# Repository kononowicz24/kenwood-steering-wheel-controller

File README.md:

# kenwood-steering-wheel-controller
This is a project to adapt the Audi A8 D2 FL multifunction steering wheel to be able to control a Kenwood car audio from the steering wheel controls. 
The large part of the code bases on https://init6.pomorze.pl/projects/kenwood_ford/ and was adapted to feature pin change interrupts on key presses.

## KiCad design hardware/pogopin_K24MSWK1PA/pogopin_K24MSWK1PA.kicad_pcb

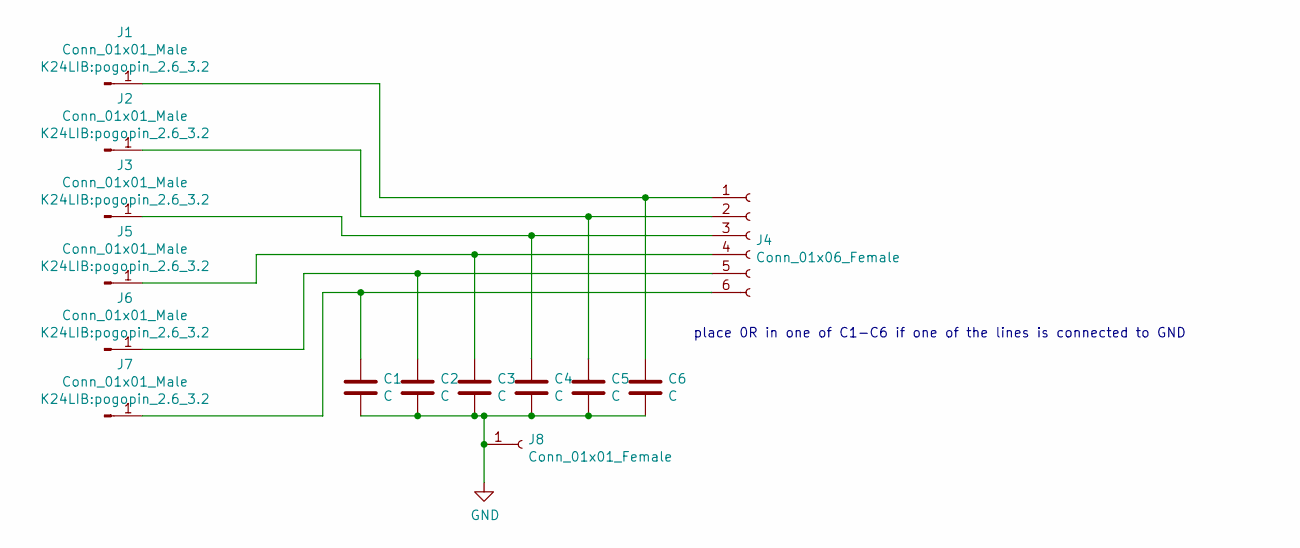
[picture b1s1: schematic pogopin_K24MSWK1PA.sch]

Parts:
C1, C2, C3, C4, C5, C6: C; C_0805_2012Metric
J1, J2, J3, J5, J6, J7: Conn_01x01_Male; pogopin_2.6_3.2
J4: Conn_01x06_Female; JST_PH_S6B-PH-K_1x06_P2.00mm_Horizontal
J8: Conn_01x01_Female; SolderWire-0.75sqmm_1x01_D1.25mm_OD3.5mm

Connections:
GND: C1.2, C2.2, C3.2, C4.2, C5.2, C6.2, J8.1
unnamed: C1.1, J4.6, J7.1
unnamed: C2.1, J4.5, J6.1
unnamed: C3.1, J4.4, J5.1
unnamed: C4.1, J3.1, J4.3
unnamed: C5.1, J2.1, J4.2
unnamed: C6.1, J1.1, J4.1

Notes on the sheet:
place 0R in one of C1-C6 if one of the lines is connected to GND

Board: 2 copper layers, 14 parts (0 on the bottom side), 7 nets, no tracks yet.

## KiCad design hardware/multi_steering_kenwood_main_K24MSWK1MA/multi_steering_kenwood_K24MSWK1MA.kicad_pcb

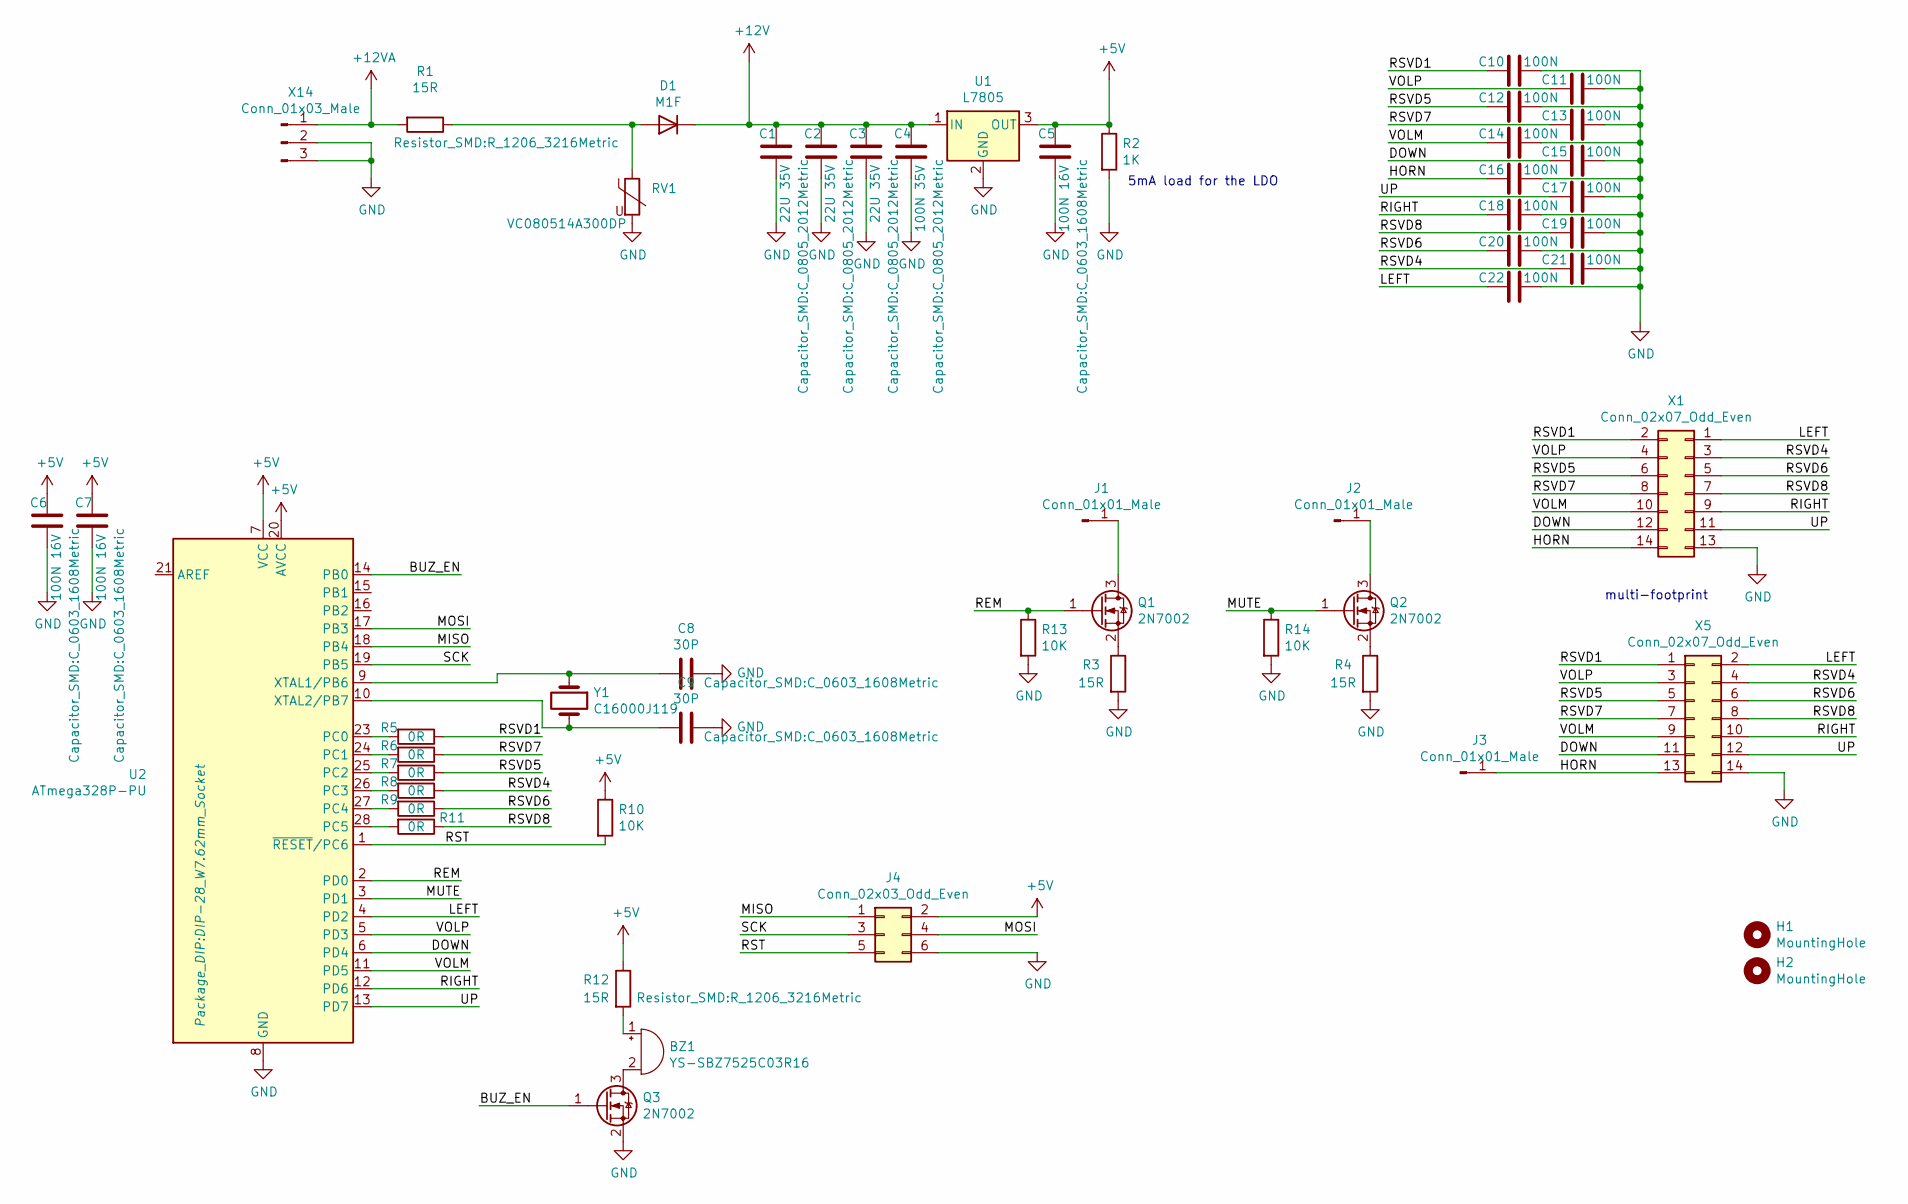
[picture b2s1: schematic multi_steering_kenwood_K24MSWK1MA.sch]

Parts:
BZ1: YS-SBZ7525C03R16; PUIAudio_SMT_0825_S_4_R
C1, C2, C3: 22U 35V; C_0805_2012Metric
C4: 100N 35V; C_0805_2012Metric
C5, C6, C7: 100N 16V; C_0603_1608Metric
C8, C9: 30P; C_0603_1608Metric
C10, C11, C12, C13, C14, C15, C16, C17, C18, C19, C20, C21, C22: 100N; C_0603_1608Metric
D1: M1F; D_SMA
H1, H2: MountingHole; MountingHole_3.2mm_M3
J1, J2, J3: Conn_01x01_Male; SpringContact_Harwin_S1941-46R
J4: Conn_02x03_Odd_Even; PinHeader_2x03_P2.54mm_Vertical
Q1, Q2, Q3: 2N7002; SOT-23
R1, R3, R4, R12: 15R; R_1206_3216Metric
R2: 1K; C_0603_1608Metric
R5, R6, R7, R8, R9, R11: 0R; R_0603_1608Metric
R10, R13, R14: 10K; C_0603_1608Metric
RV1: VC080514A300DP; R_0805_2012Metric
U1: L7805; TO-252-3_TabPin2
U2: ATmega328P-PU; DIP-28_W7.62mm_Socket
X1: Conn_02x07_Odd_Even; PinHeader_2x07_P2.00mm_Vertical_SMD
X5: Conn_02x07_Odd_Even; JST_PHD_B14B-PHDSS_2x07_P2.00mm_Vertical
X14: Conn_01x03_Male; PinHeader_1x03_P2.54mm_Vertical
Y1: C16000J119; Crystal_SMD_HC49-SD

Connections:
+5V: C5.1, C6.1, C7.1, J4.2, R2.1, R10.1, R12.1, U1.3 (OUT), U2.7 (VCC), U2.20 (AVCC)
+12V: C1.1, C2.1, C3.1, C4.1, D1.1 (K), U1.1 (IN)
+12VA: R1.2, X14.1
/BUZ_EN: Q3.1 (G), U2.14 (PB0)
/DOWN: C15.1, U2.6 (PD4), X1.12, X5.11
/HORN: C16.1, J3.1, X1.14, X5.13
/LEFT: C22.1, U2.4 (PD2), X1.1, X5.2
/MISO: J4.1, U2.18 (PB4)
/MOSI: J4.4, U2.17 (PB3)
/MUTE: Q2.1 (G), R14.1, U2.3 (PD1)
/REM: Q1.1 (G), R13.1, U2.2 (PD0)
/RIGHT: C18.1, U2.12 (PD6), X1.9, X5.10
/RST: J4.5, R10.2, U2.1 (~RESET~/PC6)
/RSVD1: C10.1, R5.1, X1.2, X5.1
/RSVD4: C21.1, R8.1, X1.3, X5.4
/RSVD5: C12.1, R7.1, X1.6, X5.5
/RSVD6: C20.1, R9.1, X1.5, X5.6
/RSVD7: C13.1, R6.1, X1.8, X5.7
/RSVD8: C19.1, R11.1, X1.7, X5.8
/SCK: J4.3, U2.19 (PB5)
/UP: C17.1, U2.13 (PD7), X1.11, X5.12
/VOLM: C14.1, U2.11 (PD5), X1.10, X5.9
/VOLP: C11.1, U2.5 (PD3), X1.4, X5.3
GND: C1.2, C2.2, C3.2, C4.2, C5.2, C6.2, C7.2, C8.1, C9.1, C10.2, C11.2, C12.2, C13.2, C14.2, C15.2, C16.2, C17.2, C18.2, C19.2, C20.2, C21.2, C22.2, J4.6, Q3.2 (S), R2.2, R3.2, R4.2, R13.2, R14.2, RV1.2, U1.2 (GND), U2.8 (GND), U2.22 (GND), X1.13, X5.14, X14.2, X14.3
unnamed: BZ1.1 (-), R12.2
unnamed: BZ1.2 (+), Q3.3 (D)
unnamed: C8.2, U2.9 (XTAL1/PB6), Y1.1
unnamed: C9.2, U2.10 (XTAL2/PB7), Y1.2
unnamed: D1.2 (A), R1.1, RV1.1
unnamed: J1.1, Q1.3 (D)
unnamed: J2.1, Q2.3 (D)
unnamed: Q1.2 (S), R3.1
unnamed: Q2.2 (S), R4.1
unnamed: R5.2, U2.23 (PC0)
unnamed: R6.2, U2.24 (PC1)
unnamed: R7.2, U2.25 (PC2)
unnamed: R8.2, U2.26 (PC3)
unnamed: R9.2, U2.27 (PC4)
unnamed: R11.2, U2.28 (PC5)

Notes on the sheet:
5mA load for the LDO
multi-footprint

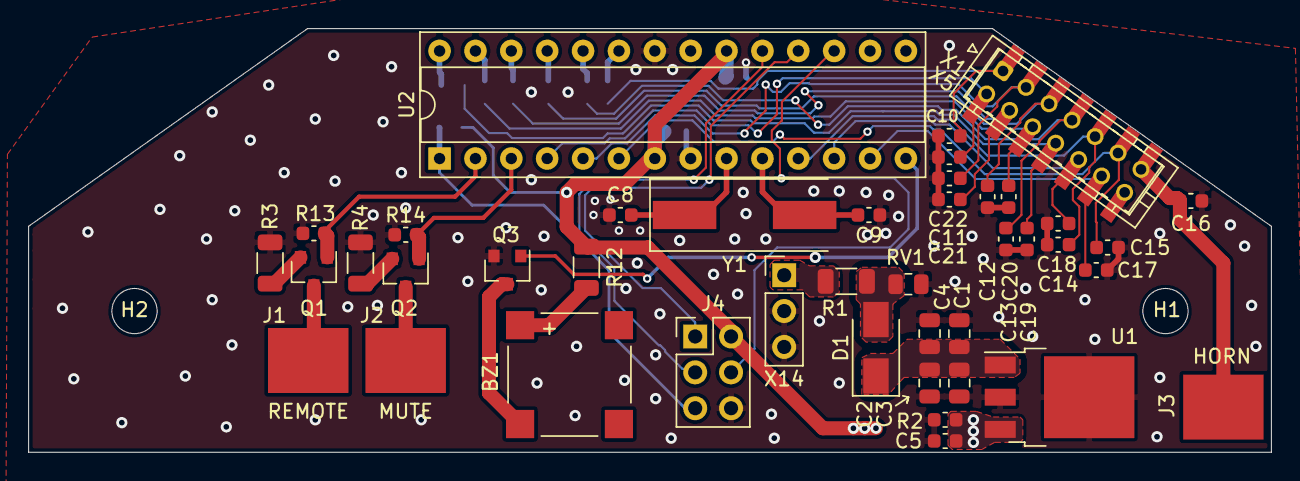
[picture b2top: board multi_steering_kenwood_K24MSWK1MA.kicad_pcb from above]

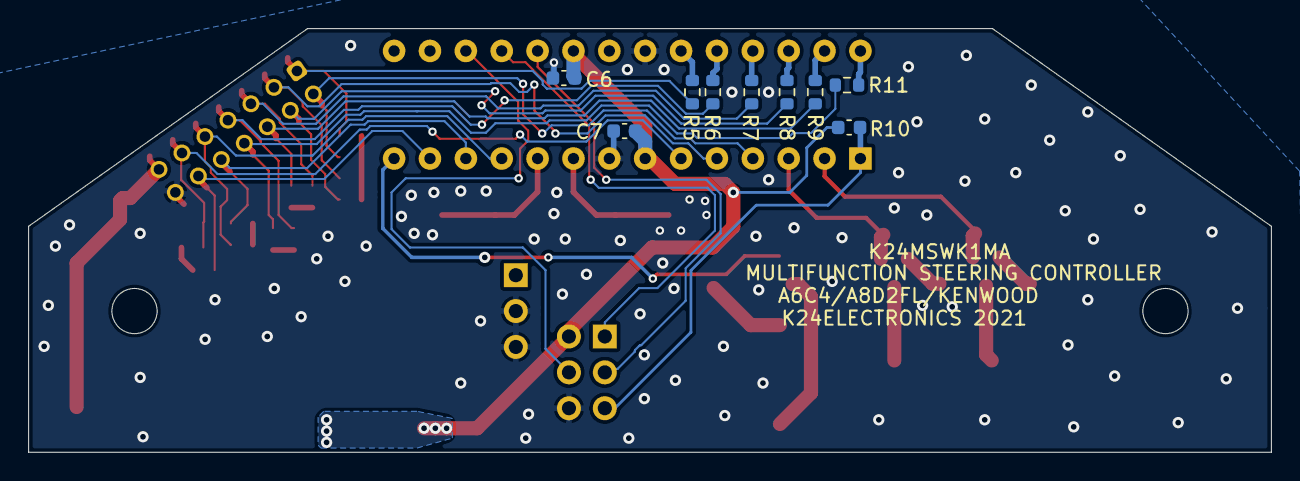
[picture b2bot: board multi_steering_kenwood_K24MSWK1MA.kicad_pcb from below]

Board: 2 copper layers, 88.0 x 30.0 mm, 54 parts (9 on the bottom side), 39 nets.

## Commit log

2023-05-19 added author note
2023-09-28 move code to /firmware
2023-09-28 update .gitignore for Kicad
2023-09-28 Added main PCB HW design files (rev.A)
2023-09-28 rename folders, set up pogopin board project
2023-09-30 finished sch, started components layout
